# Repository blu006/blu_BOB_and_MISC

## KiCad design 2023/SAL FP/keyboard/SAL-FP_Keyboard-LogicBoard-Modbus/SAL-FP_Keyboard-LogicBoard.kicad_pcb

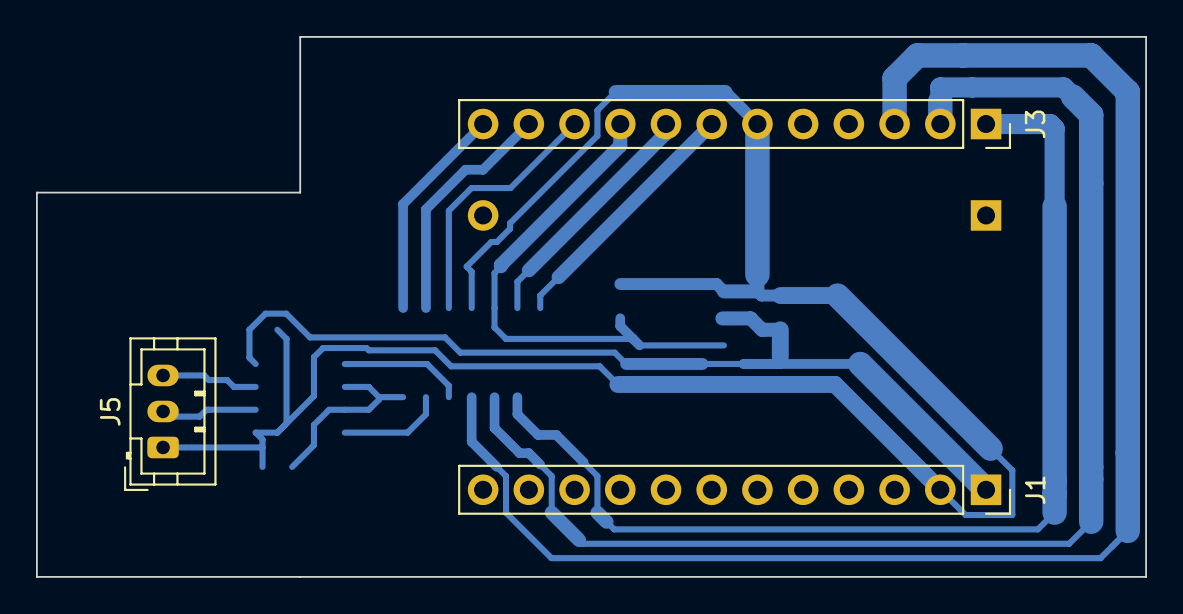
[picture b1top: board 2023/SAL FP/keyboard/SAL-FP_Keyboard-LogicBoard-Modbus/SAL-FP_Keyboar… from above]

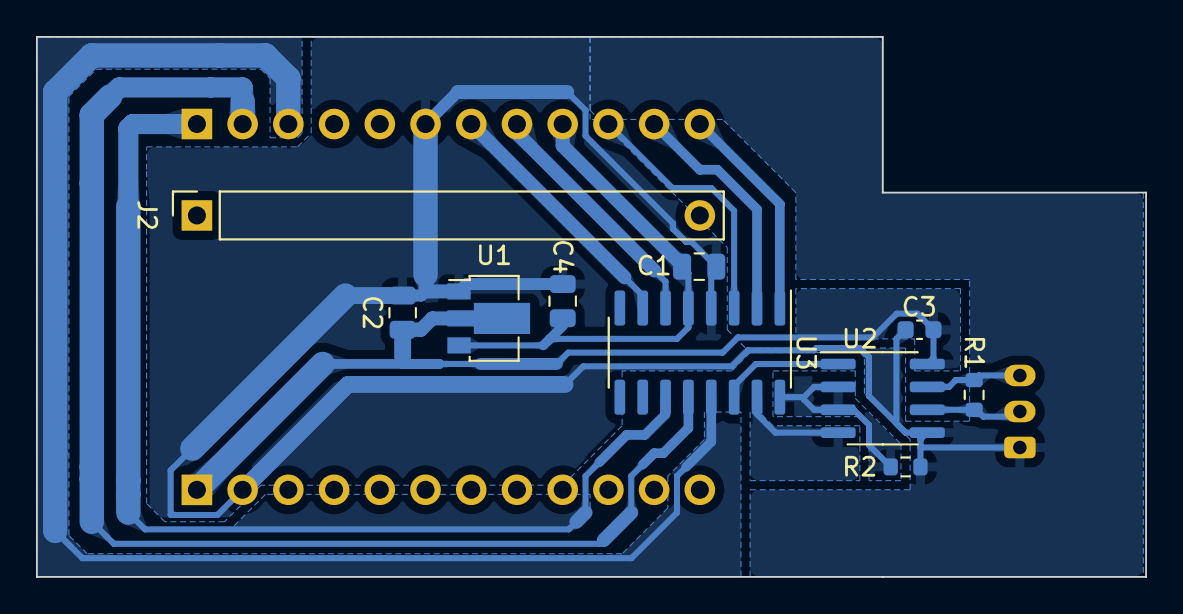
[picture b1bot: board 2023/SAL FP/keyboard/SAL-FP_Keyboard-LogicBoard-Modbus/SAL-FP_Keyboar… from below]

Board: 2 copper layers, 61.6 x 30.0 mm, 13 parts (10 on the bottom side), 16 nets.

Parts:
C1, C2, C4: 1u; C_0805_2012Metric
C3: 100n; C_0603_1608Metric
J1, J2, J3: Conn_01x12_Pin; PinSocket_1x12_P2.54mm_Vertical
J5: RS485; JST_PH_B3B-PH-K_1x03_P2.00mm_Vertical
R1: 120; R_0603_1608Metric
R2: 100k; R_0603_1608Metric
U1: MCP1700x-330xxMB; SOT-89-3
U2: MAX3485; SOIC-8_3.9x4.9mm_P1.27mm
U3: EFM8BB10F8G-A-SOIC16; SOIC-16_3.9x9.9mm_P1.27mm

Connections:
+3V3: C1.1, C4.1, J3.9, U1.3 (VO), U3.5 (VDD)
/C2CK: J3.8, U3.6 (RSTb/C2CK)
/C2D: J3.7, U3.7 (P2.0/C2D)
/LED1: J3.12, U3.1 (P0.2)
/LED2: J3.11, U3.2 (P0.1)
/LED3: J3.10, U3.3 (P0.0)
/LED4: J3.3, U3.13 (P0.6)
/LED5: J3.1, U3.11 (P1.0)
/LED6: J3.2, U3.12 (P0.7)
/RS485_DIR: R2.1, U2.2 (~RE), U2.3 (DE), U3.16 (P0.3)
/UART_RX: U2.1 (RO), U3.14 (P0.5)
/UART_TX: U2.4 (DI), U3.15 (P0.4)
GND: C1.2, C2.2, C3.2, C4.2, J1.2, J3.6, J5.1, R2.2, U1.1 (GND), U2.5 (GND), U3.4 (GND)
unnamed: J5.2, R1.2, U2.6 (A)
unnamed: J5.3, R1.1, U2.7 (B)
VDD: C2.1, C3.1, J1.1, U1.2 (VI), U2.8 (VCC)

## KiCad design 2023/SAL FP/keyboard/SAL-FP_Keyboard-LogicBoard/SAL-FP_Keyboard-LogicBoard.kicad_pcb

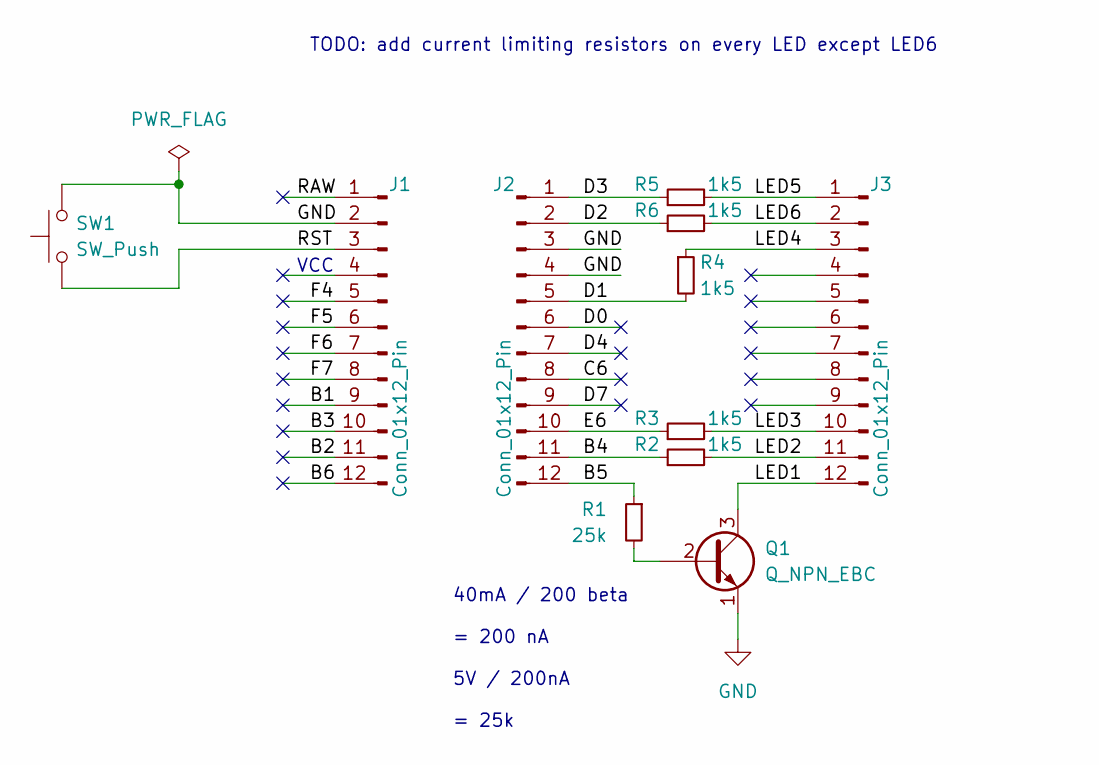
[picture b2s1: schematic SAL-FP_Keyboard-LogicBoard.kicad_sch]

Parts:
J1, J2, J3: Conn_01x12_Pin; PinSocket_1x12_P2.54mm_Vertical
Q1: Q_NPN_EBC; TO-92
R1: 25k; R_0603_1608Metric
R2, R3, R4, R5, R6: 1k5; R_0603_1608Metric
SW1: SW_Push; SW_PUSH_6mm

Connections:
/B1: J1.9
/B2: J1.11
/B3: J1.10
/B4: J2.11, R2.1
/B5: J2.12, R1.1
/B6: J1.12
/C6: J2.8
/D0: J2.6
/D1: J2.5, R4.2
/D2: J2.2, R6.1
/D3: J2.1, R5.1
/D4: J2.7
/D7: J2.9
/E6: J2.10, R3.1
/F4: J1.5
/F5: J1.6
/F6: J1.7
/F7: J1.8
/LED1: J3.12, Q1.3 (C)
/LED2: J3.11, R2.2
/LED3: J3.10, R3.2
/LED4: J3.3, R4.1
/LED5: J3.1, R5.2
/LED6: J3.2, R6.2
/RAW: J1.1
/RST: J1.3, SW1.1
GND: J1.2, J2.3, J2.4, Q1.1 (E), SW1.2
unnamed: Q1.2 (B), R1.2

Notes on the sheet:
VCC
40mA / 200 beta = 200 nA 5V / 200nA = 25k
TODO: add current limiting resistors on every LED except LED6

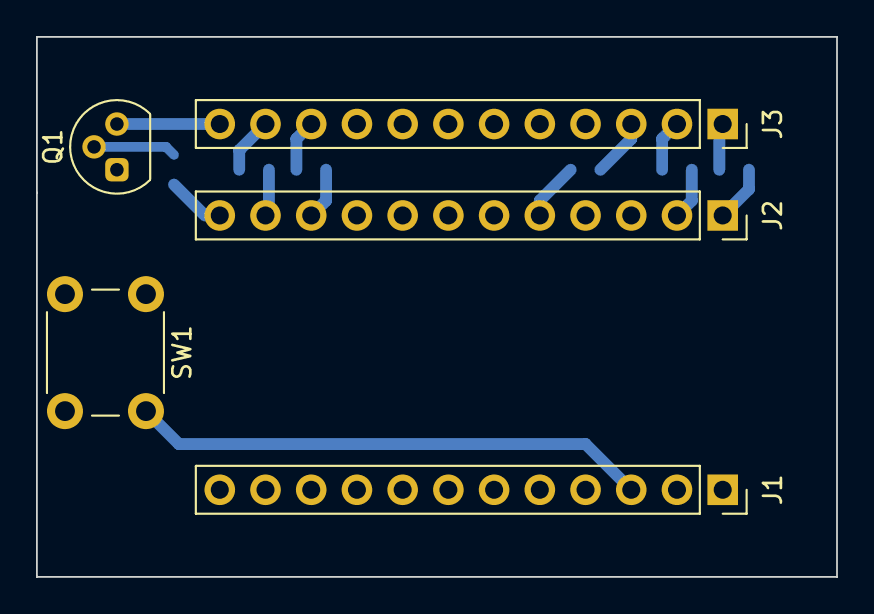
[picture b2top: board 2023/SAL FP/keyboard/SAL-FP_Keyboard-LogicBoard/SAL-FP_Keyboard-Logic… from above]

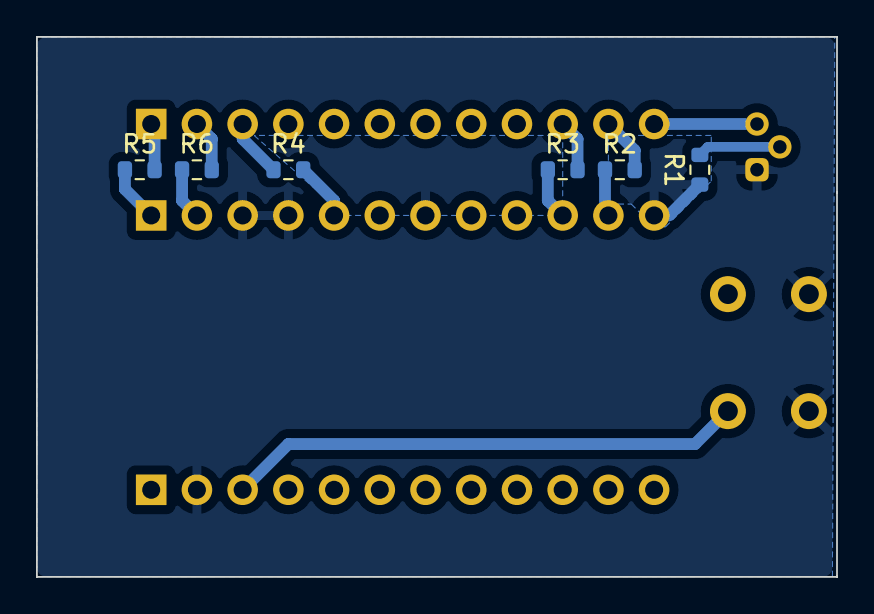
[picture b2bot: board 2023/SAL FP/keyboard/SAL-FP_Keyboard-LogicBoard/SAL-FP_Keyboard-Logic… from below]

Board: 2 copper layers, 44.5 x 30.0 mm, 11 parts (6 on the bottom side), 15 nets.

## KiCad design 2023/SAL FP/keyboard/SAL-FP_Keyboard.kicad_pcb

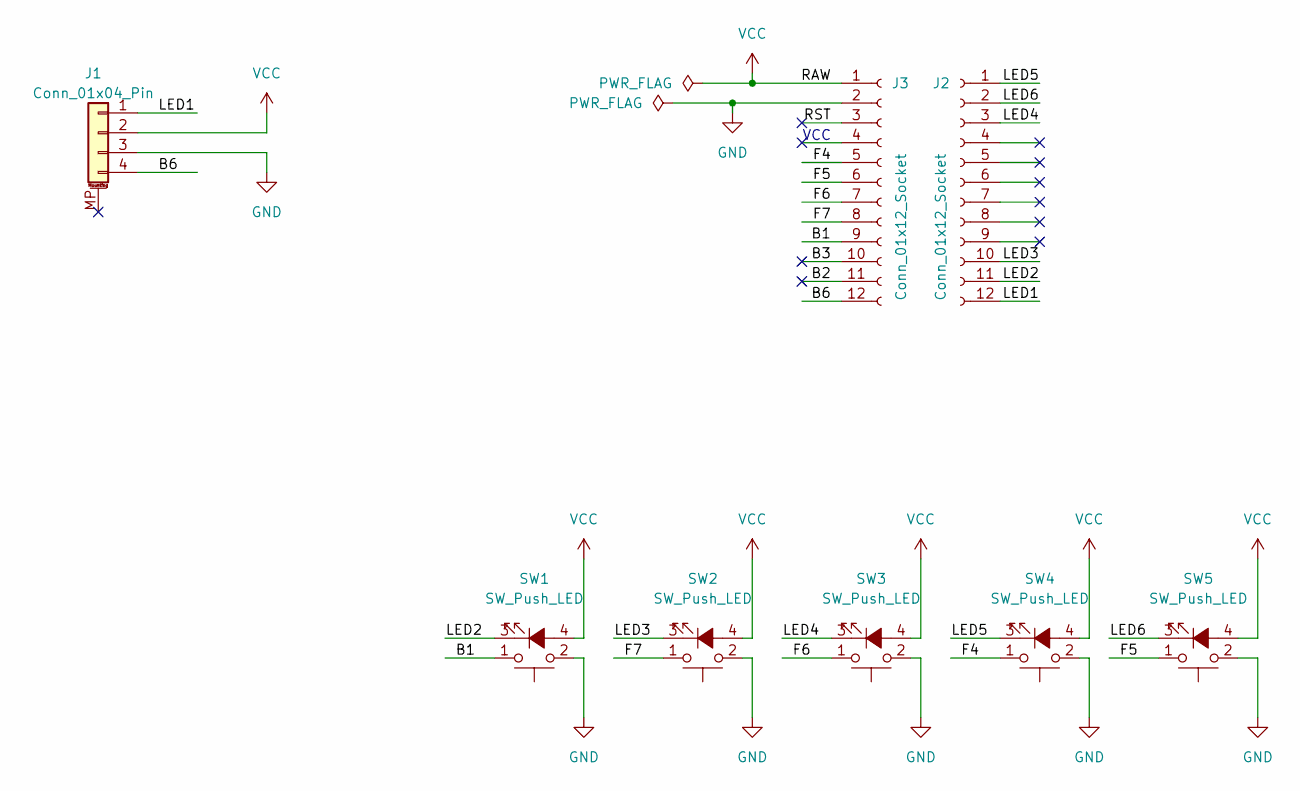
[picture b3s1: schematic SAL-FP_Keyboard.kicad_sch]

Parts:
J1: Conn_01x04_Pin; JST_PH_B4B-PH-SM4-TB_1x04-1MP_P2.00mm_Vertical
J2: Conn_01x12_Socket; PinSocket_1x12_P2.54mm_Vertical_SMD_Pin1Left
J3: Conn_01x12_Socket; PinSocket_1x12_P2.54mm_Vertical_SMD_Pin1Right
SW1, SW2, SW3, SW4, SW5: SW_Push_LED; SW_Cherry_MX_1.00u_PCB_LED

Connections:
/B1: J3.9, SW1.1
/B2: J3.11
/B3: J3.10
/B6: J1.4, J3.12
/F4: J3.5, SW4.1
/F5: J3.6, SW5.1
/F6: J3.7, SW3.1
/F7: J3.8, SW2.1
/LED1: J1.1, J2.12
/LED2: J2.11, SW1.3 (K)
/LED3: J2.10, SW2.3 (K)
/LED4: J2.3, SW3.3 (K)
/LED5: J2.1, SW4.3 (K)
/LED6: J2.2, SW5.3 (K)
/RST: J3.3
GND: J1.3, J3.2, SW1.2, SW2.2, SW3.2, SW4.2, SW5.2
VCC: J1.2, J3.1, SW1.4 (A), SW2.4 (A), SW3.4 (A), SW4.4 (A), SW5.4 (A)

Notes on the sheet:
VCC

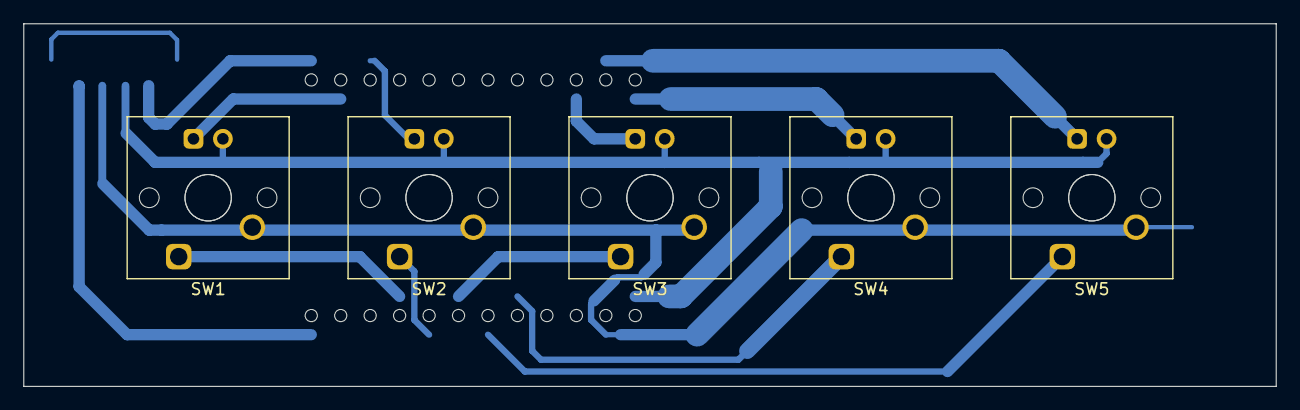
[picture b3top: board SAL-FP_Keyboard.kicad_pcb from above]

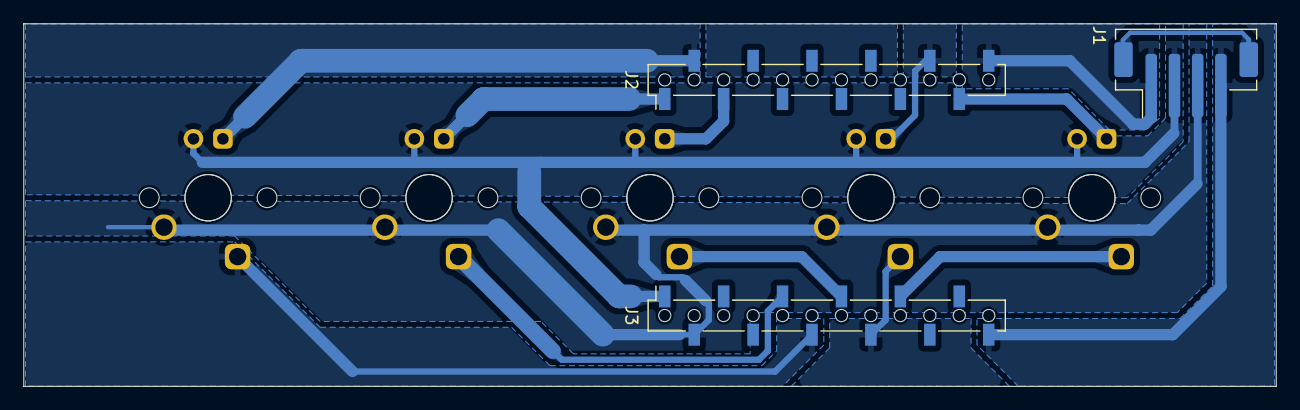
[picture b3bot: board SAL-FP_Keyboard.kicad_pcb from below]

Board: 2 copper layers, 108.0 x 31.3 mm, 8 parts (3 on the bottom side), 14 nets.

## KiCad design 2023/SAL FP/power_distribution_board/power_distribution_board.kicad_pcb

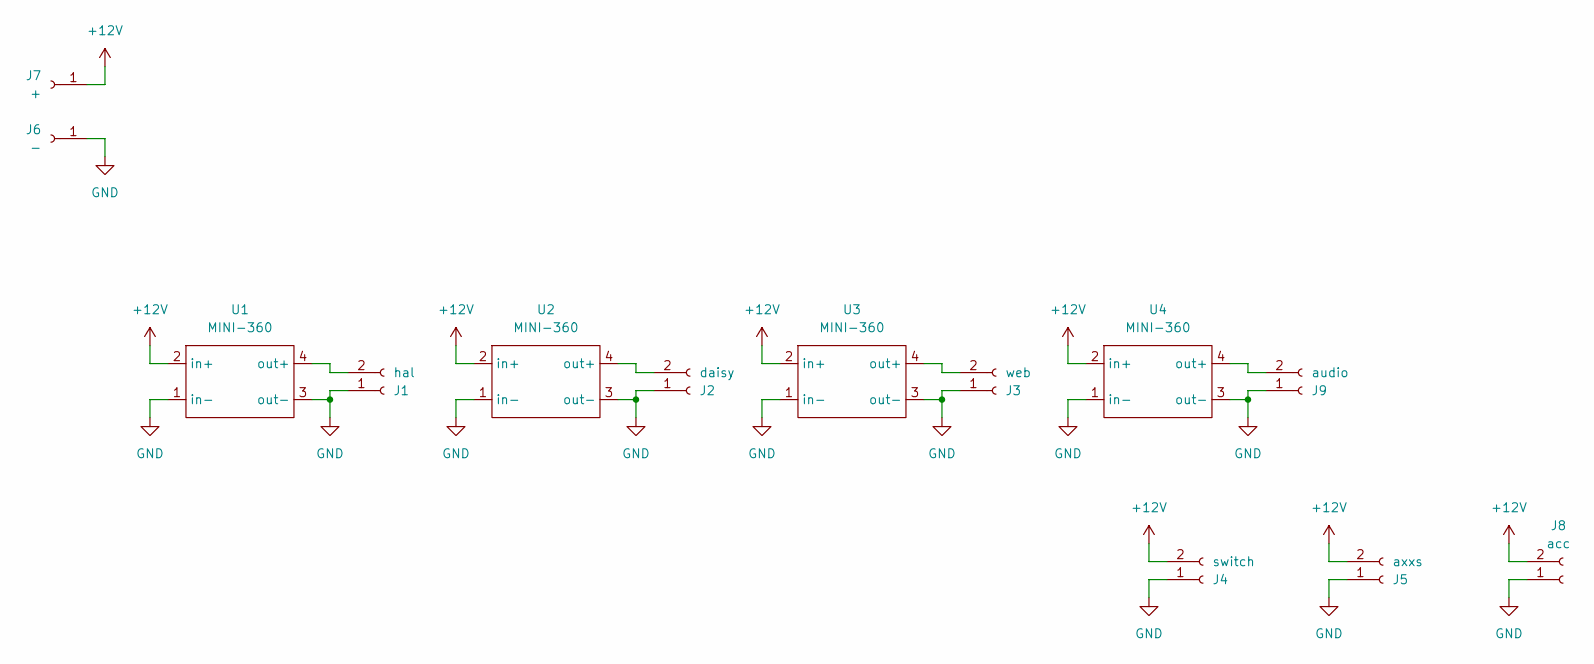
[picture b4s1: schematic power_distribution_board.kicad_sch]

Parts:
J1: hal; AMASS_XT30U-F_1x02_P5.0mm_Vertical
J2: daisy; AMASS_XT30U-F_1x02_P5.0mm_Vertical
J3: web; AMASS_XT30U-F_1x02_P5.0mm_Vertical
J4: switch; AMASS_XT30U-F_1x02_P5.0mm_Vertical
J5: axxs; AMASS_XT30U-F_1x02_P5.0mm_Vertical
J6: -; SolderWire-2sqmm_1x01_D2mm_OD3.9mm
J7: +; SolderWire-2sqmm_1x01_D2mm_OD3.9mm
J8: acc; AMASS_XT30U-F_1x02_P5.0mm_Vertical
J9: audio; AMASS_XT30U-F_1x02_P5.0mm_Vertical
U1, U2, U3, U4: MINI-360

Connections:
+12V: J4.2, J5.2, J7.1, J8.2, U1.2 (in+), U2.2 (in+), U3.2 (in+), U4.2 (in+)
GND: J1.1, J2.1, J3.1, J4.1, J5.1, J6.1, J8.1, J9.1, U1.1 (in-), U1.3 (out-), U2.1 (in-), U2.3 (out-), U3.1 (in-), U3.3 (out-), U4.1 (in-), U4.3 (out-)
unnamed: J1.2, U1.4 (out+)
unnamed: J2.2, U2.4 (out+)
unnamed: J3.2, U3.4 (out+)
unnamed: J9.2, U4.4 (out+)

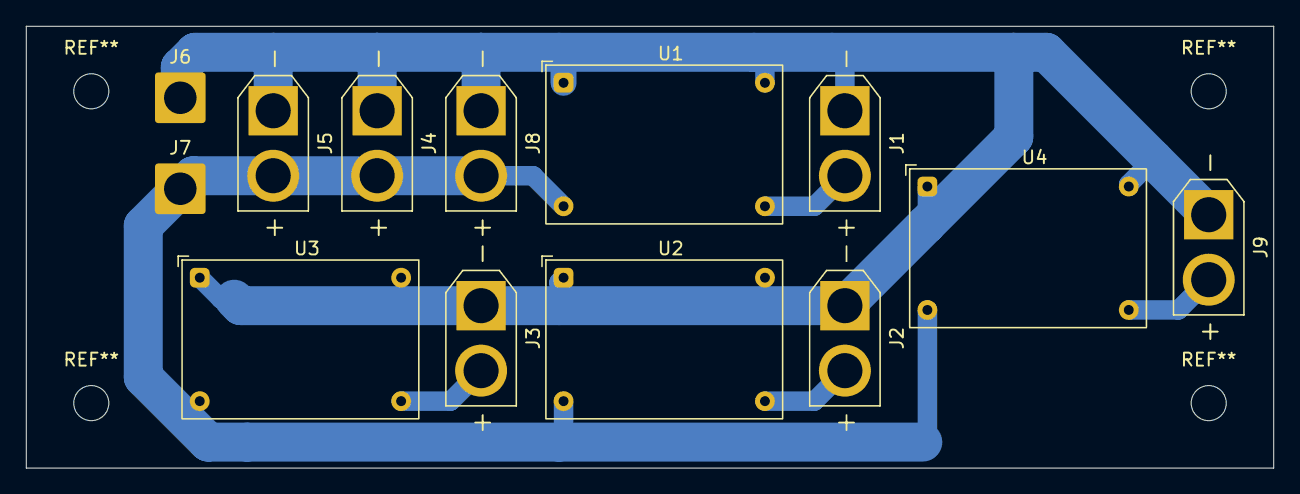
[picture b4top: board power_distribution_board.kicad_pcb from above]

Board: 2 copper layers, 96.0 x 34.0 mm, 13 parts (0 on the bottom side), 6 nets.

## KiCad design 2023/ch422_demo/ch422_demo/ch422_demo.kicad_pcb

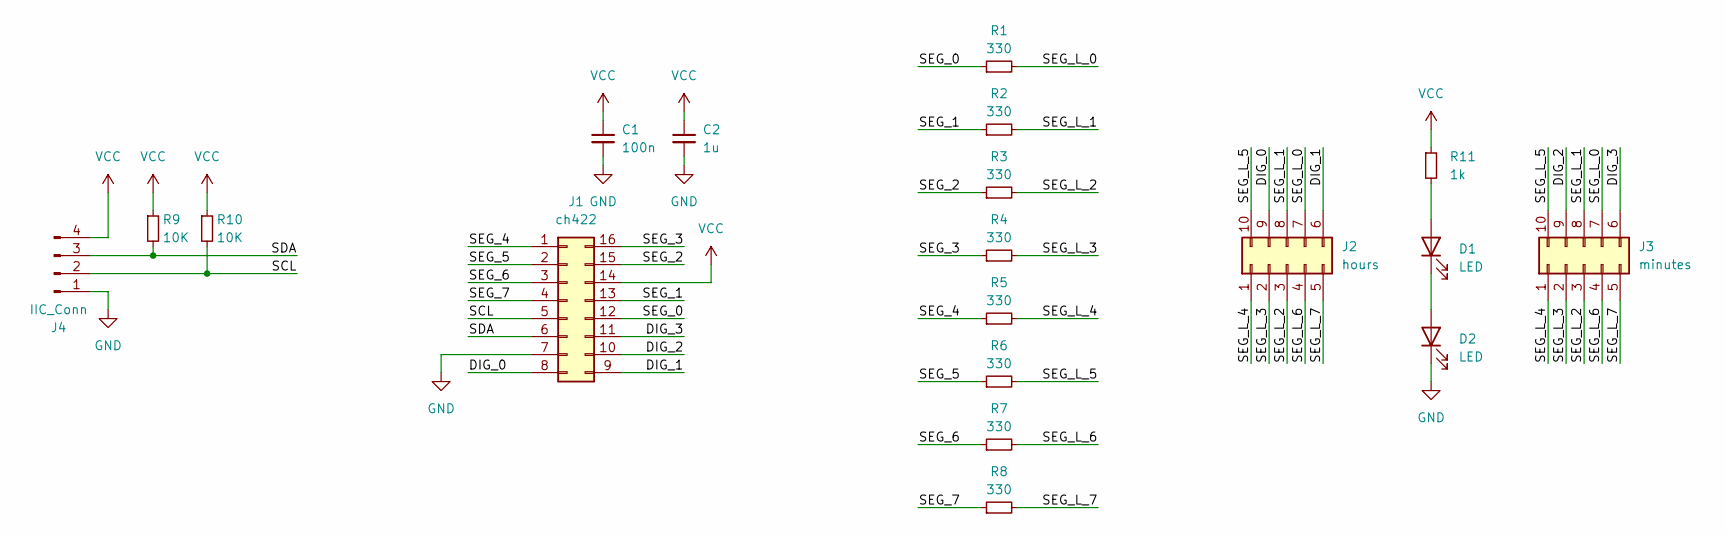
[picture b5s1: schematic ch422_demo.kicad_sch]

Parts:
C1: 100n; C_0603_1608Metric
C2: 1u; C_0805_2012Metric
D1, D2: LED; LED_D3.0mm
J1: ch422; SO-16_3.9x9.9mm_P1.27mm
J2: hours; DIP-10_W7.62mm
J3: minutes; DIP-10_W7.62mm
J4: IIC_Conn; PinSocket_1x04_P2.54mm_Vertical
R1, R2, R3, R4, R5, R6, R7, R8: 330; R_0603_1608Metric
R9, R10: 10K; R_0603_1608Metric
R11: 1k; R_0603_1608Metric

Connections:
/DIG_0: J1.8, J2.9
/DIG_1: J1.9, J2.6
/DIG_2: J1.10, J3.9
/DIG_3: J1.11, J3.6
/SCL: J1.5, J4.2, R10.2
/SDA: J1.6, J4.3, R9.2
/SEG_0: J1.12, R1.1
/SEG_1: J1.13, R2.1
/SEG_2: J1.15, R3.1
/SEG_3: J1.16, R4.1
/SEG_4: J1.1, R5.1
/SEG_5: J1.2, R6.1
/SEG_6: J1.3, R7.1
/SEG_7: J1.4, R8.1
/SEG_L_0: J2.7, J3.7, R1.2
/SEG_L_1: J2.8, J3.8, R2.2
/SEG_L_2: J2.3, J3.3, R3.2
/SEG_L_3: J2.2, J3.2, R4.2
/SEG_L_4: J2.1, J3.1, R5.2
/SEG_L_5: J2.10, J3.10, R6.2
/SEG_L_6: J2.4, J3.4, R7.2
/SEG_L_7: J2.5, J3.5, R8.2
GND: C1.2, C2.2, D2.1 (K), J1.7, J4.1
unnamed: D1.2 (A), R11.2
unnamed: D1.1 (K), D2.2 (A)
VCC: C1.1, C2.1, J1.14, J4.4, R9.1, R10.1, R11.1

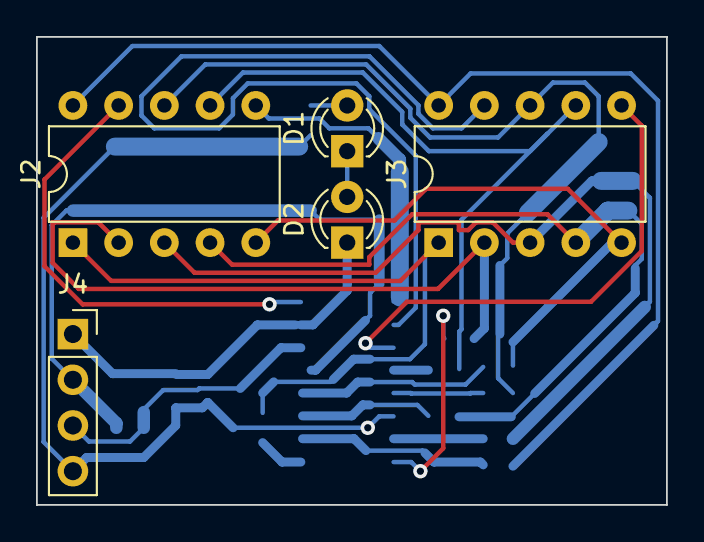
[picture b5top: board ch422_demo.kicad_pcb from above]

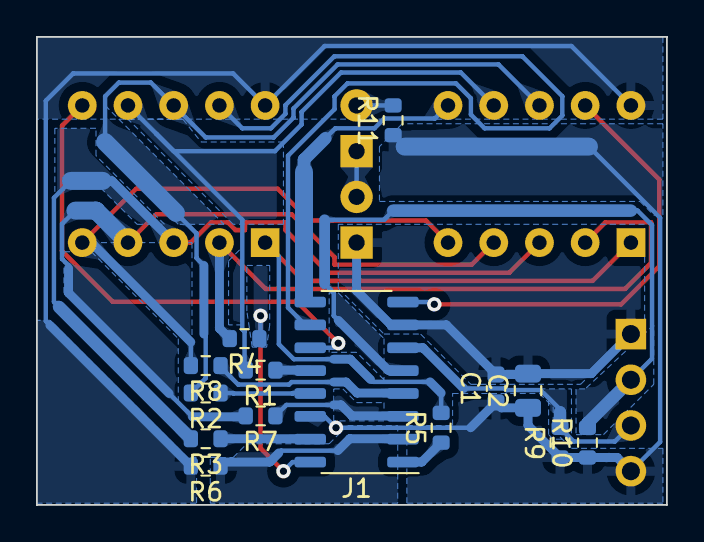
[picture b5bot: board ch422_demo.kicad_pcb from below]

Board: 2 copper layers, 35.0 x 26.0 mm, 19 parts (14 on the bottom side), 26 nets.

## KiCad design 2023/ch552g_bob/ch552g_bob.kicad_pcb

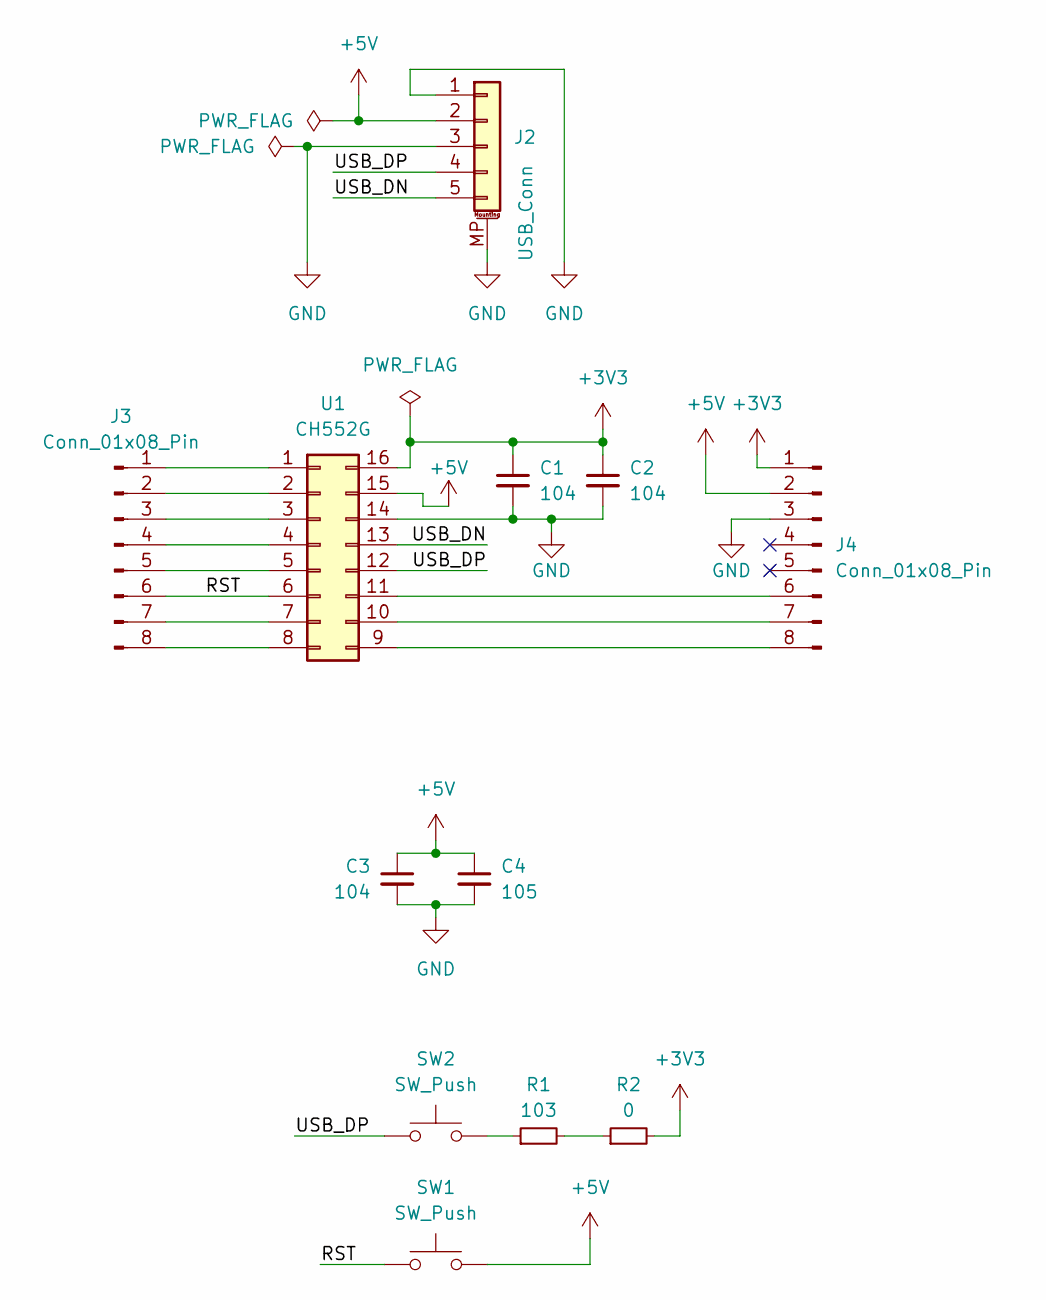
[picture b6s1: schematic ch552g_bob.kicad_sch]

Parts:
C1, C2, C3: 104; C_0603_1608Metric
C4: 105; C_0805_2012Metric
J2: USB_Conn; JST_PH_S5B-PH-SM4-TB_1x05-1MP_P2.00mm_Horizontal
J3, J4: Conn_01x08_Pin; PinHeader_1x08_P2.54mm_Vertical
R1: 103; R_0603_1608Metric
R2: 0; R_0603_1608Metric
SW1, SW2: SW_Push; SW_PUSH_6mm
U1: CH552G; SOIC-16_3.9x9.9mm_P1.27mm

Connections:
+3V3: C1.1, C2.1, J4.1, R2.2, U1.16
+5V: C3.1, C4.1, J2.2, J4.2, SW1.2, U1.15
/RST: J3.6, SW1.1, U1.6
/USB_DN: J2.5, U1.13
/USB_DP: J2.4, SW2.1, U1.12
GND: C1.2, C2.2, C3.2, C4.2, J2.1, J2.3, J2.MP (MountPin), J4.3, U1.14
unnamed: J3.1, U1.1
unnamed: J3.2, U1.2
unnamed: J3.3, U1.3
unnamed: J3.4, U1.4
unnamed: J3.5, U1.5
unnamed: J3.7, U1.7
unnamed: J3.8, U1.8
unnamed: J4.6, U1.11
unnamed: J4.7, U1.10
unnamed: J4.8, U1.9
unnamed: R1.1, SW2.2
unnamed: R1.2, R2.1

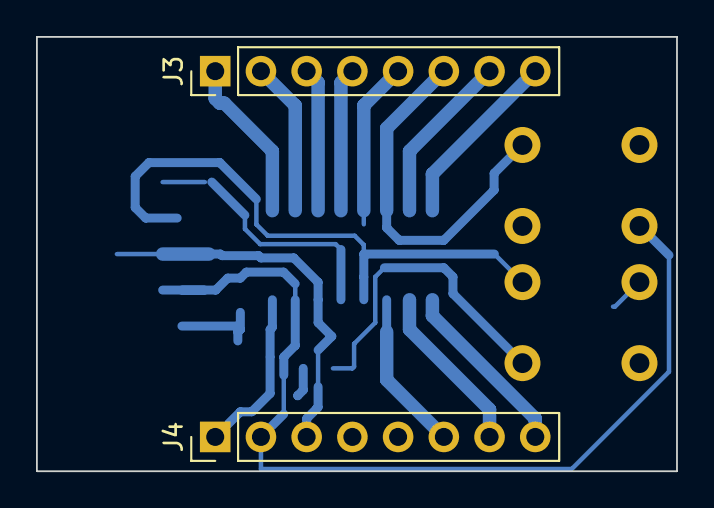
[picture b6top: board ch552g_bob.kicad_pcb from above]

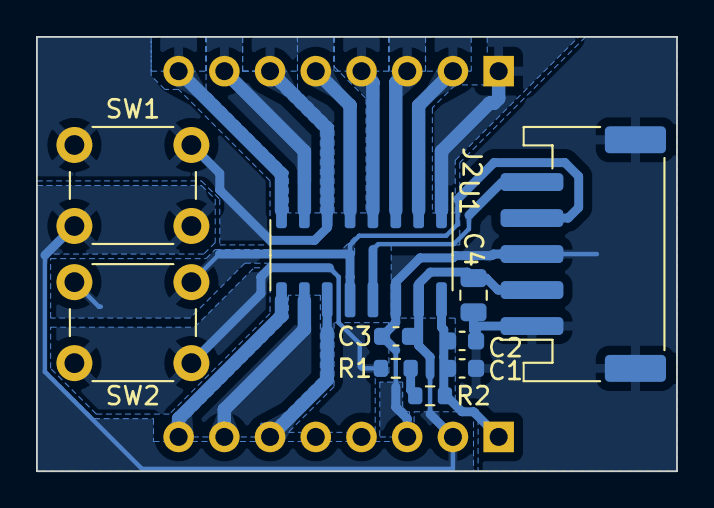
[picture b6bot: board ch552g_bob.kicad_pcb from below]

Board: 2 copper layers, 35.6 x 24.1 mm, 12 parts (10 on the bottom side), 18 nets.

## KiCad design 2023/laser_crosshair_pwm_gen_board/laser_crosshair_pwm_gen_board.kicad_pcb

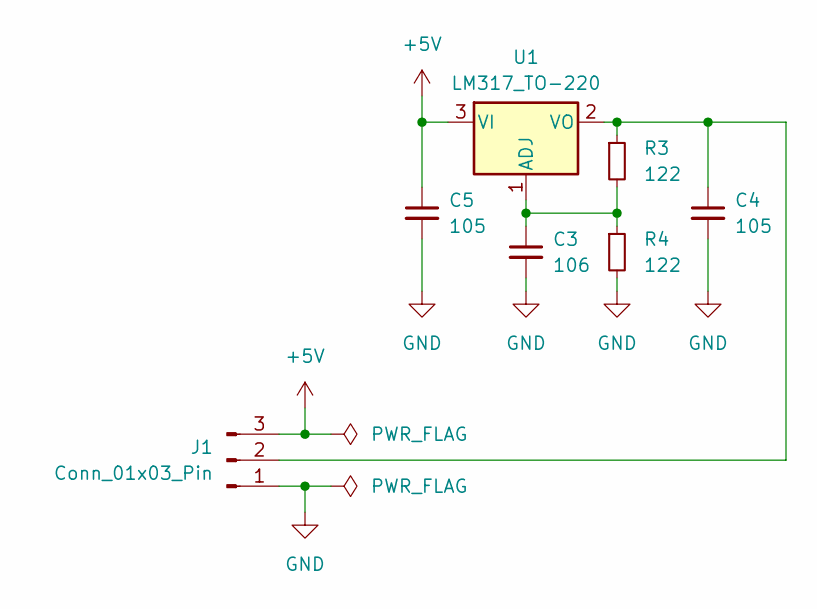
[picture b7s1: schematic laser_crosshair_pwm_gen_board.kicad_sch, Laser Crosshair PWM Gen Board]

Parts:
C3: 106; C_1206_3216Metric
C4, C5: 105; C_0805_2012Metric
J1: Conn_01x03_Pin; PinSocket_1x03_P2.54mm_Vertical
R3, R4: 122; R_0603_1608Metric
U1: LM317_TO-220; TO-220-3_Vertical

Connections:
+5V: C5.1, J1.3, U1.3 (VI)
GND: C3.2, C4.2, C5.2, J1.1, R4.2
unnamed: C4.1, J1.2, R3.1, U1.2 (VO)
unnamed: C3.1, R3.2, R4.1, U1.1 (ADJ)

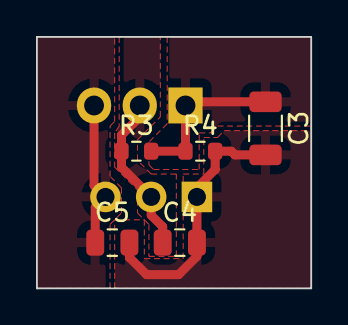
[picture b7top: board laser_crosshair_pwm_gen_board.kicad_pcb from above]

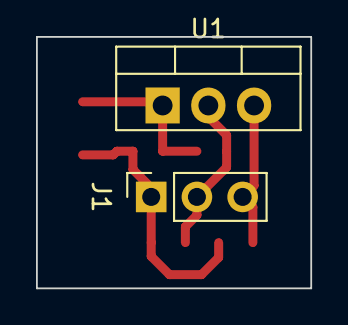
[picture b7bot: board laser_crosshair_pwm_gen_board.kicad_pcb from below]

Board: 2 copper layers, 15.2 x 14.0 mm, 7 parts (2 on the bottom side), 4 nets.

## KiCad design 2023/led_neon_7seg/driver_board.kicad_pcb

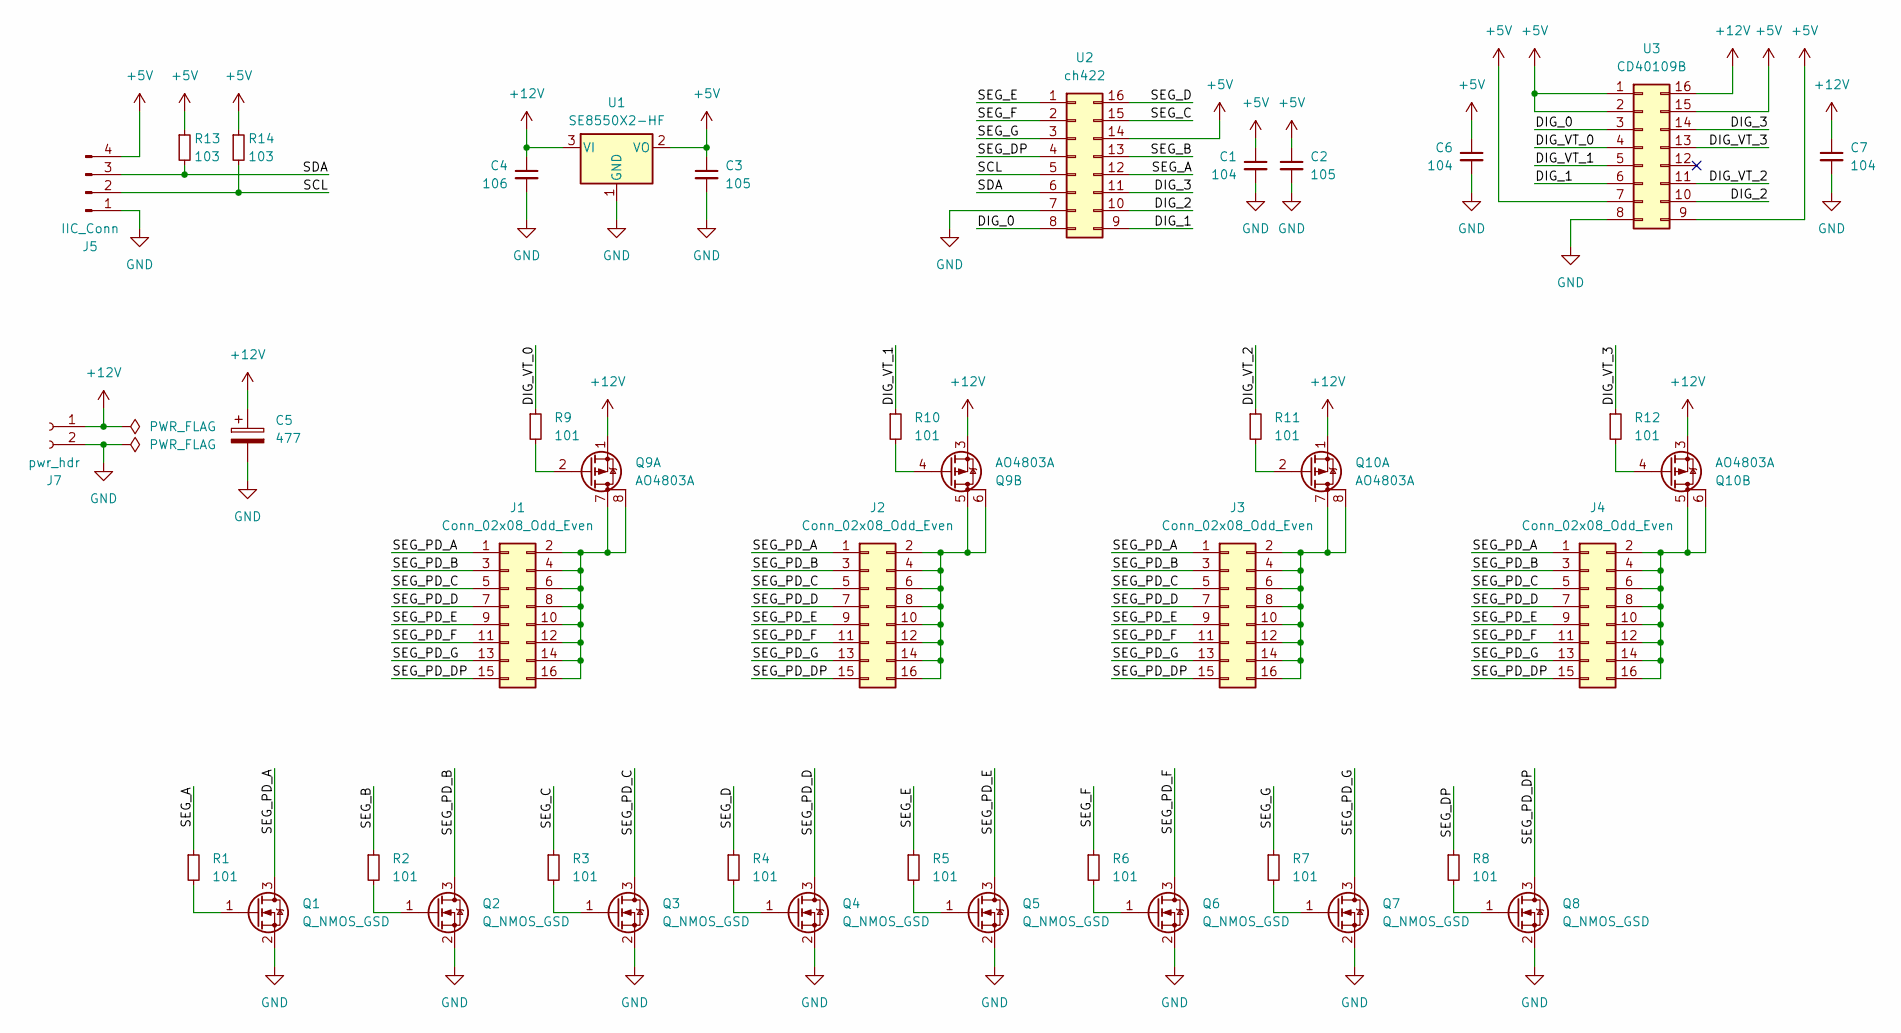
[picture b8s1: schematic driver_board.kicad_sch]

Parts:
C1, C6, C7: 104; C_0603_1608Metric
C2, C3: 105; C_0805_2012Metric
C4: 106; C_1206_3216Metric
C5: 477; CP_Radial_D7.5mm_P2.50mm
J1, J2, J3, J4: Conn_02x08_Odd_Even; PinSocket_2x08_P2.00mm_Vertical
J5: IIC_Conn; PinSocket_1x04_P2.54mm_Vertical
J7: pwr_hdr; TerminalBlock_bornier-2_P5.08mm
Q1, Q2, Q3, Q4, Q5, Q6, Q7, Q8: Q_NMOS_GSD; SOT-23
Q9, Q10: AO4803A; SOIC-8_3.9x4.9mm_P1.27mm
R1, R2, R3, R4, R5, R6, R7, R8, R9, R10, R11, R12: 101; R_0402_1005Metric
R13, R14: 103; R_0603_1608Metric
U1: SE8550X2-HF; SOT-23
U2: ch422; SO-16_3.9x9.9mm_P1.27mm
U3: CD40109B; SOIC-16W_5.3x10.2mm_P1.27mm

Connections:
+5V: C1.1, C2.1, C3.1, C6.1, J5.4, R13.1, R14.1, U1.2 (VO), U2.14, U3.1, U3.2, U3.7, U3.9, U3.15
/DIG_0: U2.8, U3.3
/DIG_1: U2.9, U3.6
/DIG_2: U2.10, U3.10
/DIG_3: U2.11, U3.14
/DIG_VT_0: R9.1, U3.4
/DIG_VT_1: R10.1, U3.5
/DIG_VT_2: R11.1, U3.11
/DIG_VT_3: R12.1, U3.13
/SCL: J5.2, R14.2, U2.5
/SDA: J5.3, R13.2, U2.6
/SEG_A: R1.1, U2.12
/SEG_B: R2.1, U2.13
/SEG_C: R3.1, U2.15
/SEG_D: R4.1, U2.16
/SEG_DP: R8.1, U2.4
/SEG_E: R5.1, U2.1
/SEG_F: R6.1, U2.2
/SEG_G: R7.1, U2.3
/SEG_PD_A: J1.1, J2.1, J3.1, J4.1, Q1.3 (D)
/SEG_PD_B: J1.3, J2.3, J3.3, J4.3, Q2.3 (D)
/SEG_PD_C: J1.5, J2.5, J3.5, J4.5, Q3.3 (D)
/SEG_PD_D: J1.7, J2.7, J3.7, J4.7, Q4.3 (D)
/SEG_PD_DP: J1.15, J2.15, J3.15, J4.15, Q8.3 (D)
/SEG_PD_E: J1.9, J2.9, J3.9, J4.9, Q5.3 (D)
/SEG_PD_F: J1.11, J2.11, J3.11, J4.11, Q6.3 (D)
/SEG_PD_G: J1.13, J2.13, J3.13, J4.13, Q7.3 (D)
unnamed: J1.2, J1.4, J1.6, J1.8, J1.10, J1.12, J1.14, J1.16, Q9.7 (D), Q9.8 (G)
unnamed: J2.2, J2.4, J2.6, J2.8, J2.10, J2.12, J2.14, J2.16, Q9.5 (D), Q9.6 (G)
unnamed: J3.2, J3.4, J3.6, J3.8, J3.10, J3.12, J3.14, J3.16, Q10.7 (D), Q10.8 (G)
unnamed: J4.2, J4.4, J4.6, J4.8, J4.10, J4.12, J4.14, J4.16, Q10.5 (D), Q10.6 (G)
unnamed: Q1.1 (G), R1.2
unnamed: Q2.1 (G), R2.2
unnamed: Q3.1 (G), R3.2
unnamed: Q4.1 (G), R4.2
unnamed: Q5.1 (G), R5.2
unnamed: Q6.1 (G), R6.2
unnamed: Q7.1 (G), R7.2
unnamed: Q8.1 (G), R8.2
unnamed: Q9.2 (G), R9.2
unnamed: Q9.4 (G), R10.2
unnamed: Q10.2 (G), R11.2
unnamed: Q10.4 (G), R12.2

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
